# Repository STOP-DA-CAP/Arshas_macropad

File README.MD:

- Overall hackpad

- Schematics

- PCB

- Case

BOM:
- 8x Cherry MX swicthes
- 2x SK6812 MINI Leds
- 1x XIAO RP2040
- 8x Blank DSA Keycaps
- 4x M3x16 Bolt
- 4x M3 Heatset
- 1x SSD1306-0.91-OLED-4pin-128x32

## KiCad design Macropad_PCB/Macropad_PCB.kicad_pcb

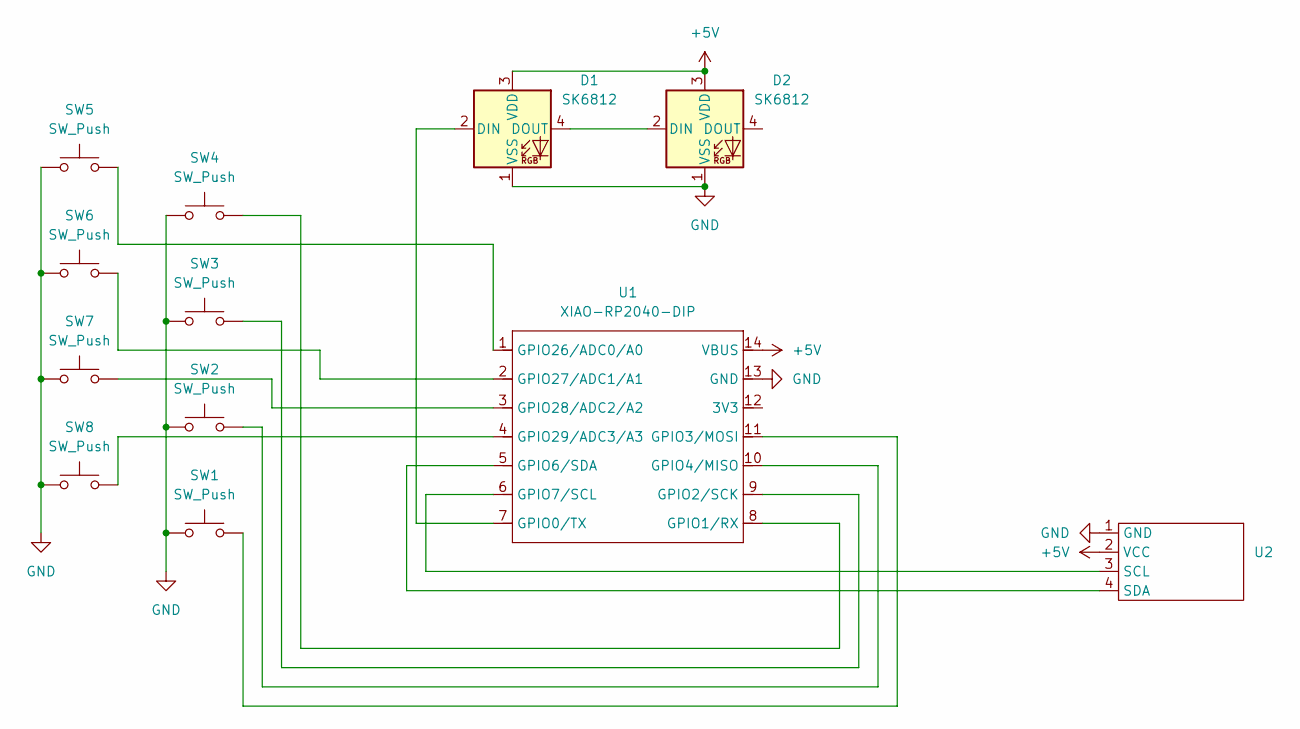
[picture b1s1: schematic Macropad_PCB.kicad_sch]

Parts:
D1, D2: SK6812; LED_SK6812_PLCC4_5.0x5.0mm_P3.2mm
SW1, SW2, SW3, SW4, SW5, SW6, SW7, SW8: SW_Push; SW_Cherry_MX_1.00u_PCB
U1: XIAO-RP2040-DIP
U2: SSD1306-0.91-OLED-4pin-128x32

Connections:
+5V: D1.3 (VDD), D2.3 (VDD), U1.14 (VBUS), U2.2 (VCC)
GND: D1.1 (VSS), D2.1 (VSS), SW1.1, SW2.1, SW3.1, SW4.1, SW5.1, SW6.1, SW7.1, SW8.1, U1.13 (GND), U2.1 (GND)
unnamed: D1.2 (DIN), U1.7 (GPIO0/TX)
unnamed: D1.4 (DOUT), D2.2 (DIN)
unnamed: SW4.2, U1.8 (GPIO1/RX)
unnamed: SW3.2, U1.9 (GPIO2/SCK)
unnamed: SW1.2, U1.11 (GPIO3/MOSI)
unnamed: SW2.2, U1.10 (GPIO4/MISO)
unnamed: U1.5 (GPIO6/SDA), U2.4 (SDA)
unnamed: U1.6 (GPIO7/SCL), U2.3 (SCL)
unnamed: SW5.2, U1.1 (GPIO26/ADC0/A0)
unnamed: SW6.2, U1.2 (GPIO27/ADC1/A1)
unnamed: SW7.2, U1.3 (GPIO28/ADC2/A2)
unnamed: SW8.2, U1.4 (GPIO29/ADC3/A3)

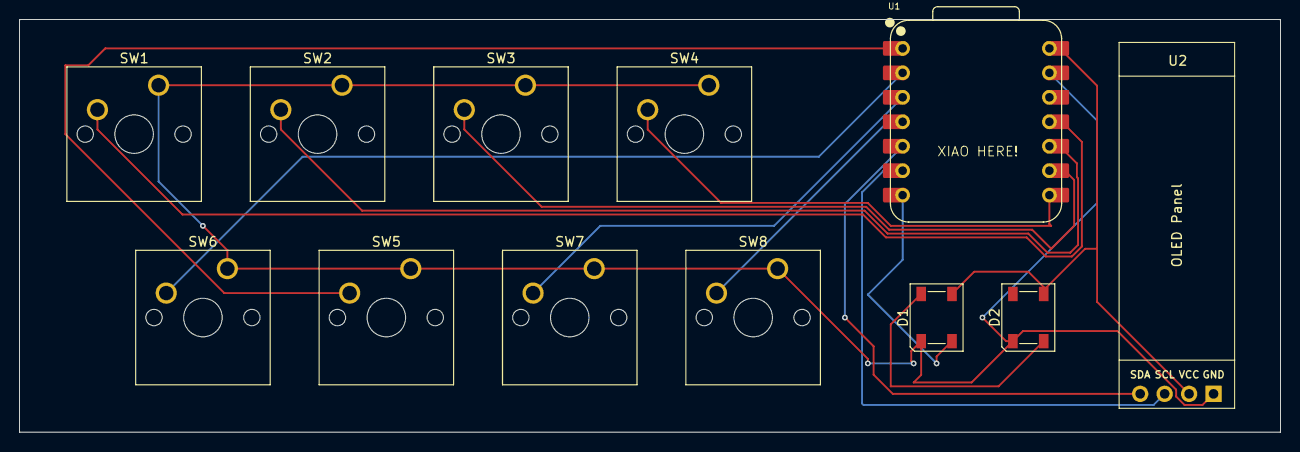
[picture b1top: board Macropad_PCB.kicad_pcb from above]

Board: 2 copper layers, 131.0 x 42.9 mm, 12 parts (0 on the bottom side), 14 nets.

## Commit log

2025-12-07 added files
2025-12-07 readme.md added
2025-12-07 updated 3d model
